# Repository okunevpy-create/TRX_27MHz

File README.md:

# TRX 27 MHz — самодельная КВ/СВ радиостанция

Модульная радиостанция диапазона 27 МГц (AM + SSB фазовым методом) для автомобиля и автономной работы.

## Назначение
- Связь на частотах дальнобойщиков (15-й канал, 27.135 МГц, AM).
- Радиолюбительские связи SSB (вызывная 27.190 МГц).

## Ограничения и риски
- **Мощность**: AM — не более 4 Вт (несущая), SSB — не более 12 Вт (пиковая). Ограничитель AM — обязателен, отключаемый через физический тумблер LIMIT/FULL на УМ.
- **Термостабильность SSB**: открытый вопрос, решается отдельной сессией (кварц Si5351 ±20 ppm).
- **Регуляторика**: безлицензионная СиБи в РФ; отключение ограничителя AM — осознанное действие пользователя.

## Этапы и подэтапы
| Этап | Название | Папка | Подэтапы |
|------|----------|-------|----------|
| **0** | Мастер-лист (интерфейсы) | `KiCad/00_master` | — |
| **1** | Плата управления | `KiCad/01_control` | 1.1–1.5 |
| **2** | Усилитель мощности | `KiCad/02_power_amp` | 2.1–2.4 |
| **3** | Тракт RX/TX | `KiCad/03_rx_tx` | 3.1–3.5 |
| **4** | Корпусирование | `Mechanical/` | 4.1–4.5 |

## Рекомендуемый порядок работ
1. **Этап 0** — мастер-лист: иерархия и все межблочные сигналы.
2. Зафиксировать контракты (`docs/contracts/`).
3. Схемотехника 1.1–1.4.
4. Схемотехника 2.1–2.2.
5. **Совместно** 1.5 + 2.3 (PTT, I_sense, SWR_sense, PWR_LIMIT_EN/SW, RX_audio).
6. ⚠️ **Только теперь** — травление и монтаж платы этапа 1.
7. Доделать 2.4 (тепловой расчёт).
8. Этап 3 (3.1–3.5).
9. Этап 4 (4.1–4.5).

> **⚠️ Важно:** изготовление платы этапа 1 (травление, монтаж) начинается **только после** завершения совместных работ 1.5 + 2.3 и фиксации контракта `control_pa.md`. До этого — только схемотехника и разводка в KiCad, без травления.

## Структура
- `docs/` — документация, контракты, BOM, расчёты.
- `Firmware/` — прошивка (PlatformIO, STM32F411).
- `KiCad/` — проекты плат, локальные библиотеки.
- `Mechanical/` — корпус, панели, крепления (FreeCAD).

## Быстрые ссылки
- [Архитектура и декомпозиция](docs/block-diagram.md)
- [Питание](docs/power-distribution.md)
- [Контракты](docs/contracts/README.md)
- [BOM](docs/bom/README.md)
- [Расчёты](docs/calculations/README.md)
- [Контекст для сессий](docs/context.md)
- [Оборудование](docs/equipment.md)
- [Распиновка](docs/inter-module-pinout.md)
- [Каналы](docs/channels.md)
- [KiCad](KiCad/README.md)
- [Прошивка](Firmware/README.md)
- [Механика](Mechanical/README.md)

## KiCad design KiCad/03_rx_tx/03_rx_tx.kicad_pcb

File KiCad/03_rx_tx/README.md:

# 03_rx_tx — тракт RX/TX (этап 3)

## Подэтапы
- **3.1** — BPF 27 МГц
- **3.2** — Смеситель + ПЧ 10 МГц + кварцевый фильтр
- **3.3** — Детектор AM/SSB + УНЧ + защита входа RX (диоды + аттенюатор); разъём `J9` (XH2.54 2P) под проводной монтаж: SP+ и GND (к корпусному разъёму 3.5 мм); вход `MUTE` (управление mute-транзистором на входе LM386)
- **3.4** — Формирователь SSB (фильтровый метод: DSB @10 МГц → кварцевый фильтр) + драйвер TX 2SC2314; модулятор принимает `MIC_LINE` с `01_control`
- **3.5** — Питание: 12 В → LM7809 → локальные LDO

## Назначение
- Смеситель на SA612.
- ПЧ 10 МГц + кварцевый фильтр.
- Детектор AM/SSB, УНЧ на LM386.
- Формирователь SSB фильтровым методом (балансный модулятор NE612 DSB @10 МГц → лестничный кварцевый фильтр).
- BPF 27 МГц.
- Защита входа RX от просачивания при передаче.

## Контракт
- `docs/contracts/control_rxtx.md` — VFO, BFO, MODE, RX_audio, PTT, 12 В.

## FM
Не делаем (решено 2026-10-31).

## Статус
Заготовка. Заполняется после этапа 2.

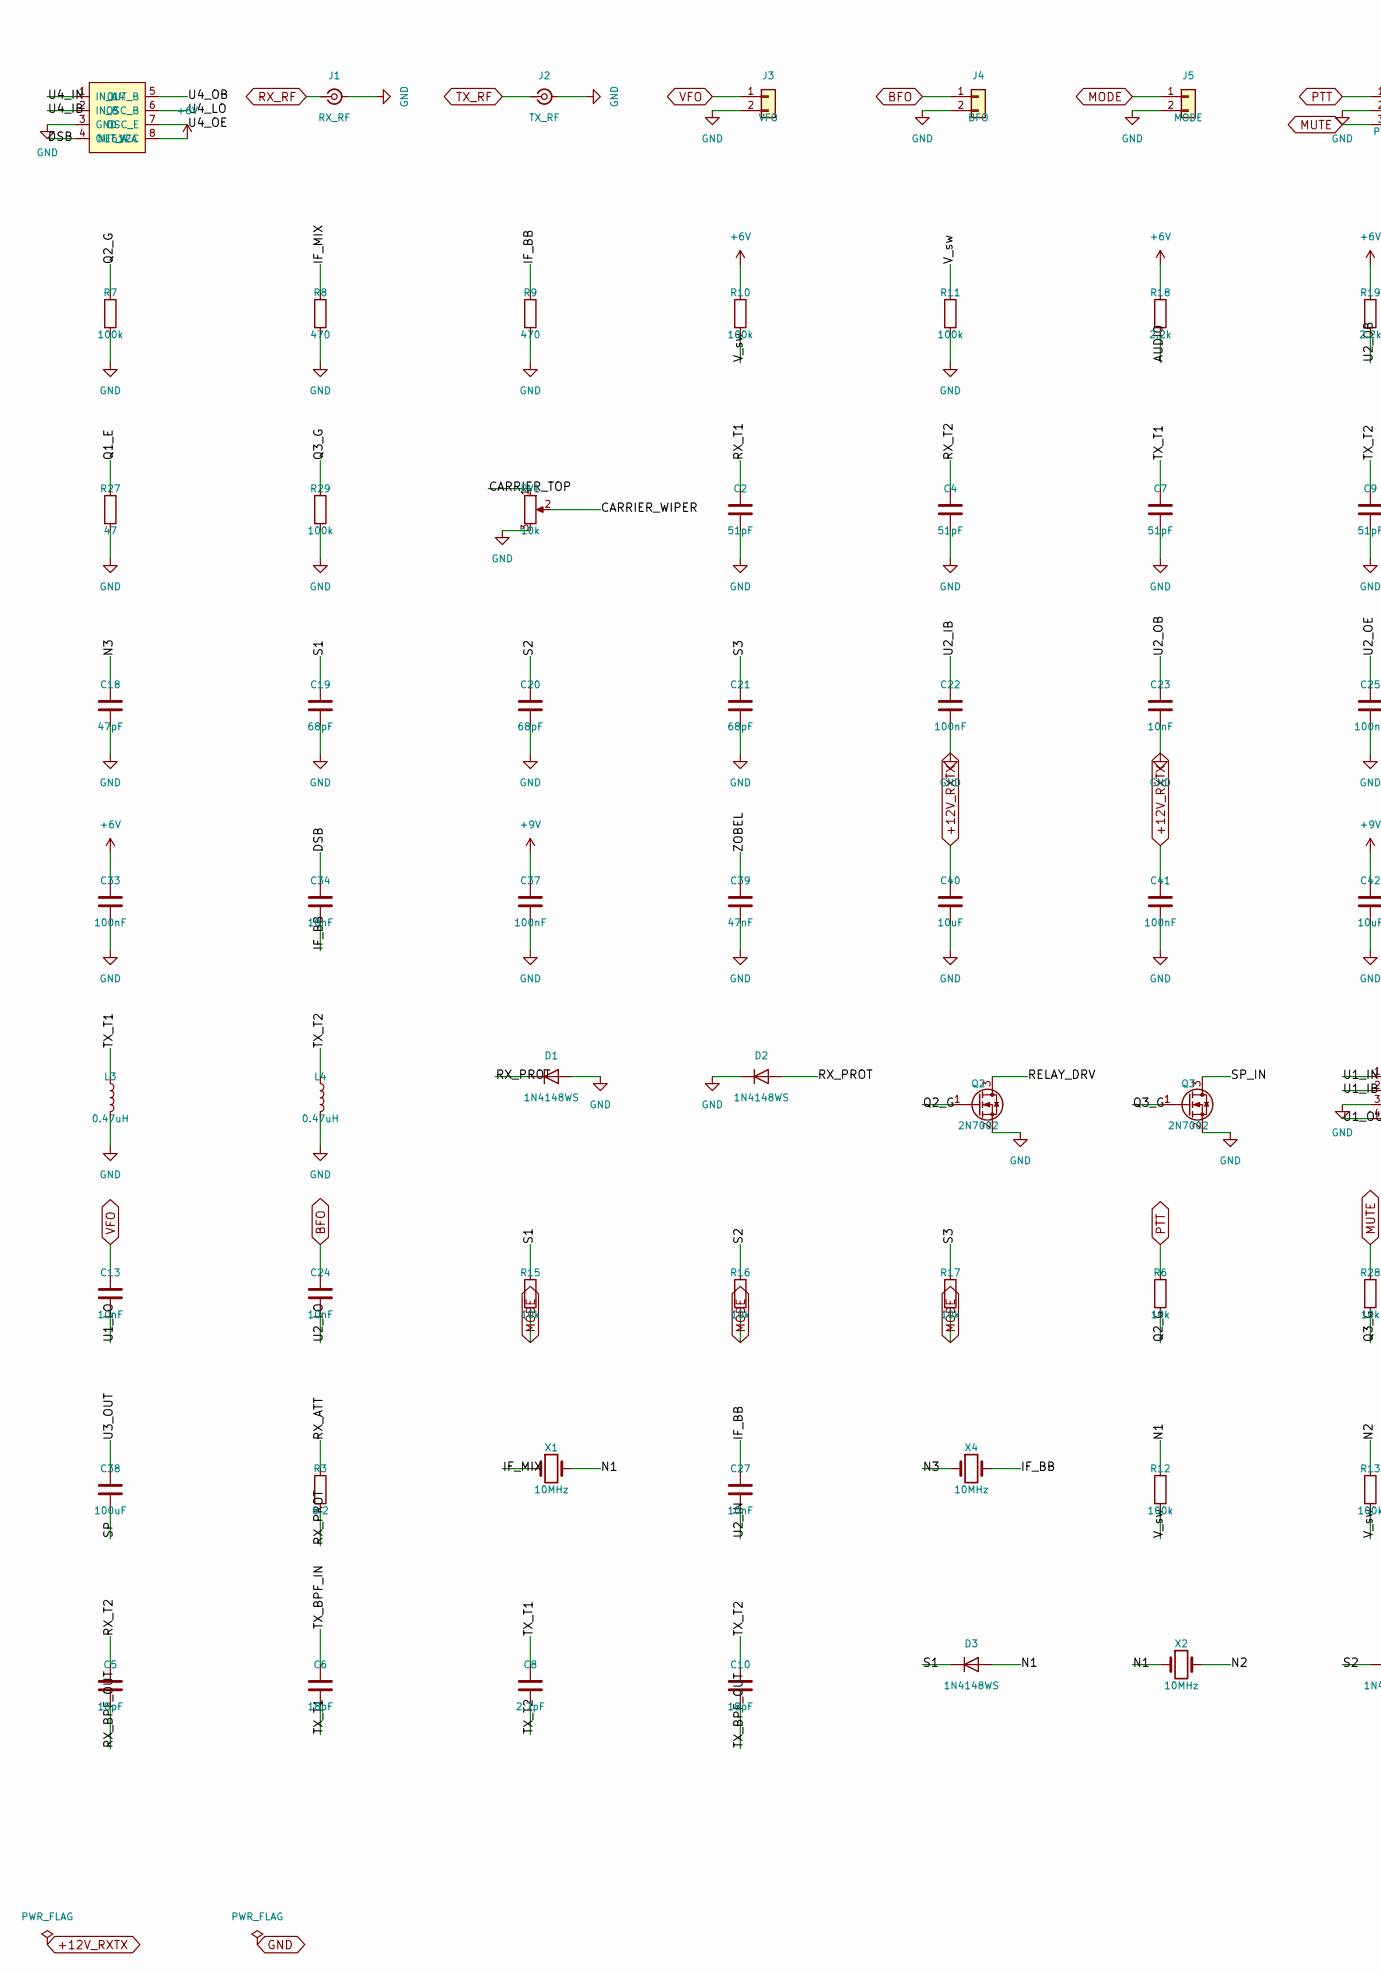
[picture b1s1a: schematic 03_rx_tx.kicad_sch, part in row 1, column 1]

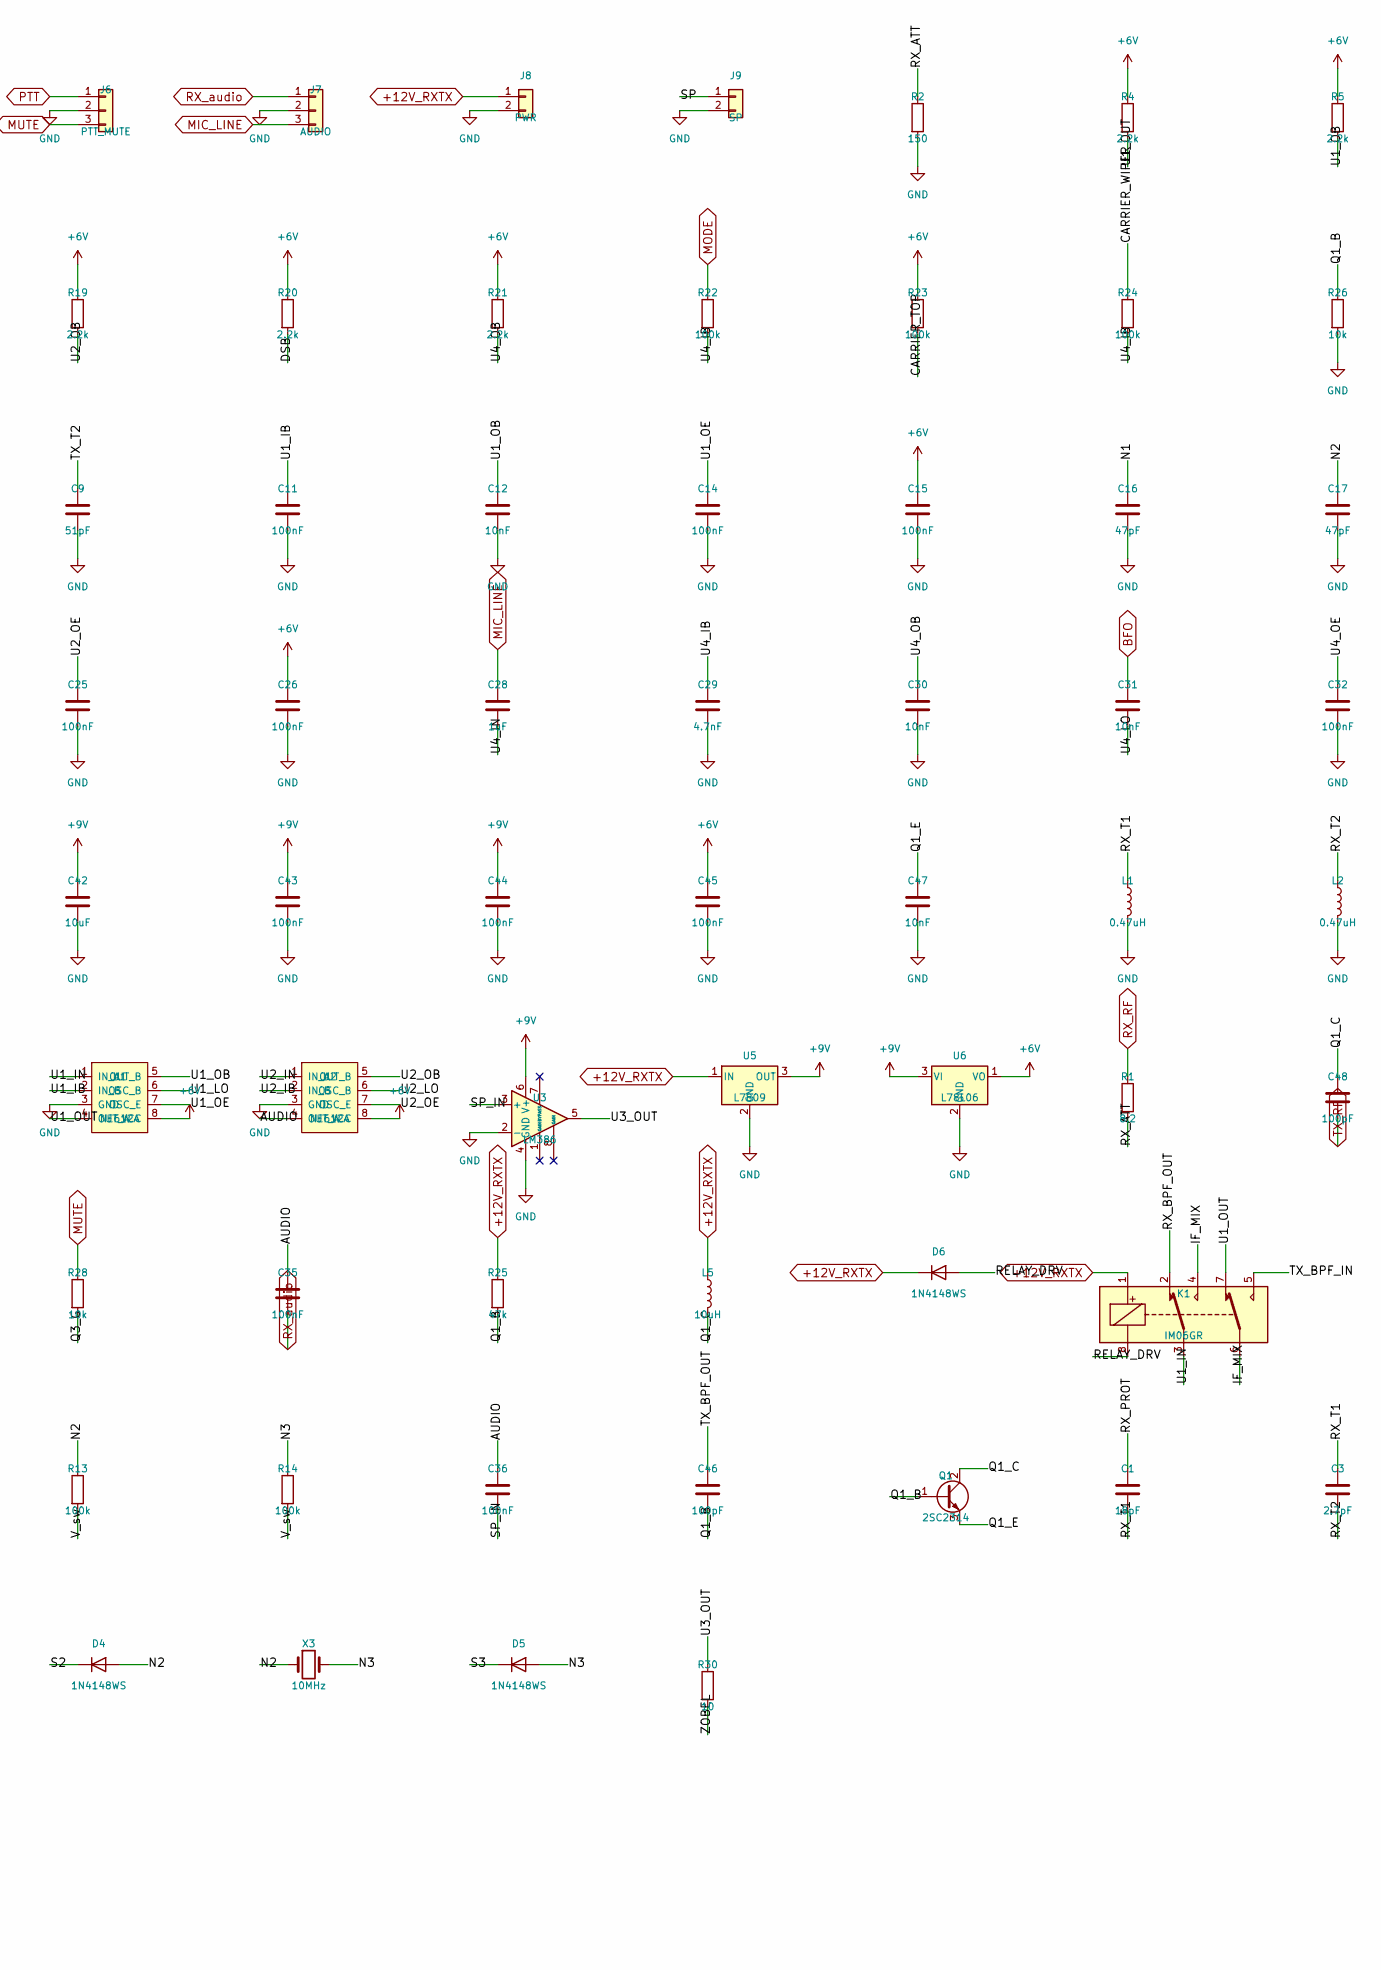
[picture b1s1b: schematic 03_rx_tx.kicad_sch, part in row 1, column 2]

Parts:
C1, C5, C6, C10: 18pF; C_0805_2012Metric_Pad1.18x1.45mm_HandSolder
C2, C4, C7, C9: 51pF; C_0805_2012Metric_Pad1.18x1.45mm_HandSolder
C3, C8: 2.7pF; C_0805_2012Metric_Pad1.18x1.45mm_HandSolder
C11, C14, C15, C22, C25, C26, C32, C33, C35, C36, C37, C41, C43, C44, C45: 100nF; C_0603_1608Metric_Pad1.08x0.95mm_HandSolder
C12, C13, C23, C24, C27, C30, C31, C34, C47: 10nF; C_0603_1608Metric_Pad1.08x0.95mm_HandSolder
C16, C17, C18: 47pF; C_0603_1608Metric_Pad1.08x0.95mm_HandSolder
C19, C20, C21: 68pF; C_0603_1608Metric_Pad1.08x0.95mm_HandSolder
C28: 1uF; C_0603_1608Metric_Pad1.08x0.95mm_HandSolder
C29: 4.7nF; C_0603_1608Metric_Pad1.08x0.95mm_HandSolder
C38: 100uF; CP_Elec_6.3x5.3
C39: 47nF; C_0603_1608Metric_Pad1.08x0.95mm_HandSolder
C40, C42: 10uF; CP_Elec_6.3x5.3
C46, C48: 100pF; C_0603_1608Metric_Pad1.08x0.95mm_HandSolder
D1, D2, D3, D4, D5, D6: 1N4148WS; D_SOD-323F
J1: RX_RF; SMA_S-P215
J2: TX_RF; SMA_S-P215
J3: VFO; SMA_S-P215
J4: BFO; SMA_S-P215
J5: MODE; JST_XH_B2B-XH-A_1x02_P2.50mm_Vertical
J6: PTT_MUTE; JST_XH_B3B-XH-A_1x03_P2.50mm_Vertical
J7: AUDIO; JST_XH_B3B-XH-A_1x03_P2.50mm_Vertical
J8: PWR; TerminalBlock_Phoenix_MKDS-1,5-2_1x02_P5.00mm_Horizontal
J9: SP; JST_XH_B2B-XH-A_1x02_P2.50mm_Vertical
K1: IM06GR; Relay_DPDT_AXICOM_IM06GR_GullWing
L1, L2, L3, L4: 0.47uH; L_0805_2012Metric_Pad1.05x1.20mm_HandSolder
L5: 10uH; L_0805_2012Metric_Pad1.05x1.20mm_HandSolder
Q1: 2SC2314; TO-92L_HandSolder
Q2, Q3: 2N7002; SOT-23_Handsoldering
R1, R3: 8.2; R_0603_1608Metric_Pad0.98x0.95mm_HandSolder
R2: 150; R_0603_1608Metric_Pad0.98x0.95mm_HandSolder
R4, R5, R18, R19, R20, R21: 2.2k; R_0603_1608Metric_Pad0.98x0.95mm_HandSolder
R6, R15, R16, R17, R26, R28: 10k; R_0603_1608Metric_Pad0.98x0.95mm_HandSolder
R7, R10, R11, R12, R13, R14, R22, R23, R24, R29: 100k; R_0603_1608Metric_Pad0.98x0.95mm_HandSolder
R8, R9: 470; R_0603_1608Metric_Pad0.98x0.95mm_HandSolder
R25: 47k; R_0603_1608Metric_Pad0.98x0.95mm_HandSolder
R27: 47; R_0603_1608Metric_Pad0.98x0.95mm_HandSolder
R30: 10; R_0603_1608Metric_Pad0.98x0.95mm_HandSolder
RV1: 10k; Potentiometer_Bourns_3214W_Vertical
U1, U2, U4: NE612A; SOIC-8_3.9x4.9mm_P1.27mm
U3: LM386; SOIC-8_3.9x4.9mm_P1.27mm
U5: L7809; TO-220-3_Vertical
U6: L78L06; TO-92_Inline
X1, X2, X3, X4: 10MHz; Crystal_SMD_HC49-SD_HandSoldering

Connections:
+6V: C15.1, C26.1, C33.1, C45.1, R4.1, R5.1, R10.1, R18.1, R19.1, R20.1, R21.1, R23.1, U1.8 (VCC), U2.8 (VCC), U4.8 (VCC), U6.1 (VO)
+9V: C37.1, C42.1, C43.1, C44.1, U3.6 (V+), U5.3 (OUT), U6.3 (VI)
+12V_RXTX: C40.1, C41.1, D6.1 (K), J8.1, K1.1, L5.1, R25.1, U5.1 (IN)
/AUDIO: C35.1, C36.1, R18.2, U2.4 (OUT_A)
/CARRIER_TOP: R23.2, RV1.1
/CARRIER_WIPER: R24.1, RV1.2
/DSB: C34.1, R20.2, U4.4 (OUT_A)
/IF_BB: C27.1, C34.2, R9.1, X4.2
/IF_MIX: K1.4, K1.6, R8.1, X1.1
/N1: C16.1, D3.2 (A), R12.1, X1.2, X2.1
/N2: C17.1, D4.2 (A), R13.1, X2.2, X3.1
/N3: C18.1, D5.2 (A), R14.1, X3.2, X4.1
/Q1_B: C46.2, Q1.1 (B), R25.2, R26.1
/Q1_C: C48.1, L5.2, Q1.2 (C)
/Q1_E: C47.1, Q1.3 (E), R27.1
/Q2_G: Q2.1 (G), R6.2, R7.1
/Q3_G: Q3.1 (G), R28.2, R29.1
/RELAY_DRV: D6.2 (A), K1.8, Q2.3 (D)
/RX_ATT: R1.2, R2.1, R3.1
/RX_BPF_OUT: C5.2, K1.2
/RX_PROT: C1.1, D1.1 (K), D2.2 (A), R3.2
/RX_T1: C1.2, C2.1, C3.1, L1.1
/RX_T2: C3.2, C4.1, C5.1, L2.1
/S1: C19.1, D3.1 (K), R15.1
/S2: C20.1, D4.1 (K), R16.1
/S3: C21.1, D5.1 (K), R17.1
/SP: C38.2, J9.1
/SP_IN: C36.2, Q3.3 (D), U3.3 (+)
/TX_BPF_IN: C6.1, K1.5
/TX_BPF_OUT: C10.2, C46.1
/TX_T1: C6.2, C7.1, C8.1, L3.1
/TX_T2: C8.2, C9.1, C10.1, L4.1
/U1_IB: C11.1, U1.2 (IN_B)
/U1_IN: K1.3, U1.1 (IN_A)
/U1_LO: C13.2, U1.6 (OSC_B)
/U1_OB: C12.1, R5.2, U1.5 (OUT_B)
/U1_OE: C14.1, U1.7 (OSC_E)
/U1_OUT: K1.7, R4.2, U1.4 (OUT_A)
/U2_IB: C22.1, U2.2 (IN_B)
/U2_IN: C27.2, U2.1 (IN_A)
/U2_LO: C24.2, U2.6 (OSC_B)
/U2_OB: C23.1, R19.2, U2.5 (OUT_B)
/U2_OE: C25.1, U2.7 (OSC_E)
/U3_OUT: C38.1, R30.1, U3.5
/U4_IB: C29.1, R22.2, R24.2, U4.2 (IN_B)
/U4_IN: C28.2, U4.1 (IN_A)
/U4_LO: C31.2, U4.6 (OSC_B)
/U4_OB: C30.1, R21.2, U4.5 (OUT_B)
/U4_OE: C32.1, U4.7 (OSC_E)
/V_sw: R10.2, R11.1, R12.2, R13.2, R14.2
/ZOBEL: C39.1, R30.2
BFO: C24.1, C31.1, J4.1
GND: C2.2, C4.2, C7.2, C9.2, C11.2, C12.2, C14.2, C15.2, C16.2, C17.2, C18.2, C19.2, C20.2, C21.2, C22.2, C23.2, C25.2, C26.2, C29.2, C30.2, C32.2, C33.2, C37.2, C39.2, C40.2, C41.2, C42.2, C43.2, C44.2, C45.2, C47.2, D1.2 (A), D2.1 (K), J1.2 (Ext), J2.2 (Ext), J3.2, J4.2, J5.2, J6.2, J7.2, J8.2, J9.2, L1.2, L2.2, L3.2, L4.2, Q2.2 (S), Q3.2 (S), R2.2, R7.2, R8.2, R9.2, R11.2, R26.2, R27.2, R29.2, RV1.3, U1.3 (GND), U2.3 (GND), U3.2 (-), U3.4 (GND), U4.3 (GND), U5.2 (GND), U6.2 (GND)
MIC_LINE: C28.1, J7.3
MODE: J5.1, R15.2, R16.2, R17.2, R22.1
MUTE: J6.3, R28.1
PTT: J6.1, R6.1
RX_RF: J1.1 (In), R1.1
RX_audio: C35.2, J7.1
TX_RF: C48.2, J2.1 (In)
VFO: C13.1, J3.1

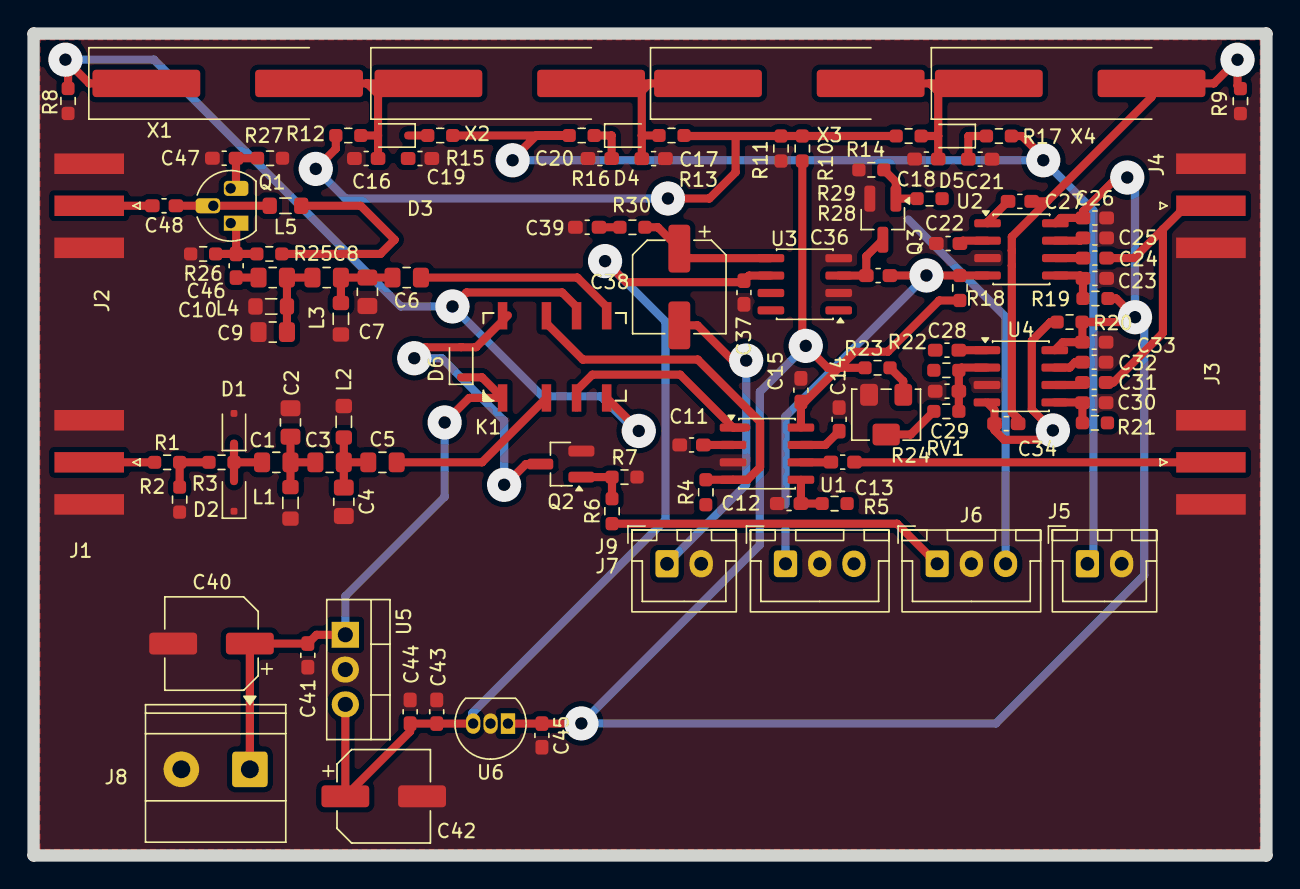
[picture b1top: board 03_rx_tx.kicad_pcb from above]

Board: 2 copper layers, 90.0 x 60.0 mm, 113 parts (1 on the bottom side), 61 nets.

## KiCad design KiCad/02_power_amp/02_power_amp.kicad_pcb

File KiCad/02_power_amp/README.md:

# 02_power_amp — усилитель мощности (этап 2)

## Подэтапы
- **2.1** — Драйвер + 2× RD16HHF1 (push-pull, класс AB)
- **2.2** — ФНЧ 27 МГц (5-го порядка)
- **2.3** — Датчики тока/КСВ + тумблер LIMIT/FULL + подстроечник + светодиод + вход PWR_LIMIT_EN + выход PWR_LIMIT_SW
- **2.4** — Тепловой расчёт + радиатор

## Назначение
- ~10–15 Вт на 50 Ом при раскачке ~0,5 Вт.
- В AM — ограничение до 4 Вт (тумблер LIMIT + подстроечник).
- Питание: 12 В напрямую через LC-фильтр.
- Радиатор обязателен.

## T/R switch и антенна
- **Реле на `02_power_amp`**, антенный разъём J_ANT_1 — здесь.
- Управление — PTT с `01_control`.

## Контракт
- `docs/contracts/control_pa.md` — PTT, I_sense, SWR_sense, PWR_LIMIT_EN, PWR_LIMIT_SW, 12 В.

## Связь с этапом 1
Подэтап **2.3** разводится совместно с **1.5**, до изготовления платы этапа 1.

## Статус
Заготовка. Схемотехника 2.1–2.2 — после 1.4.

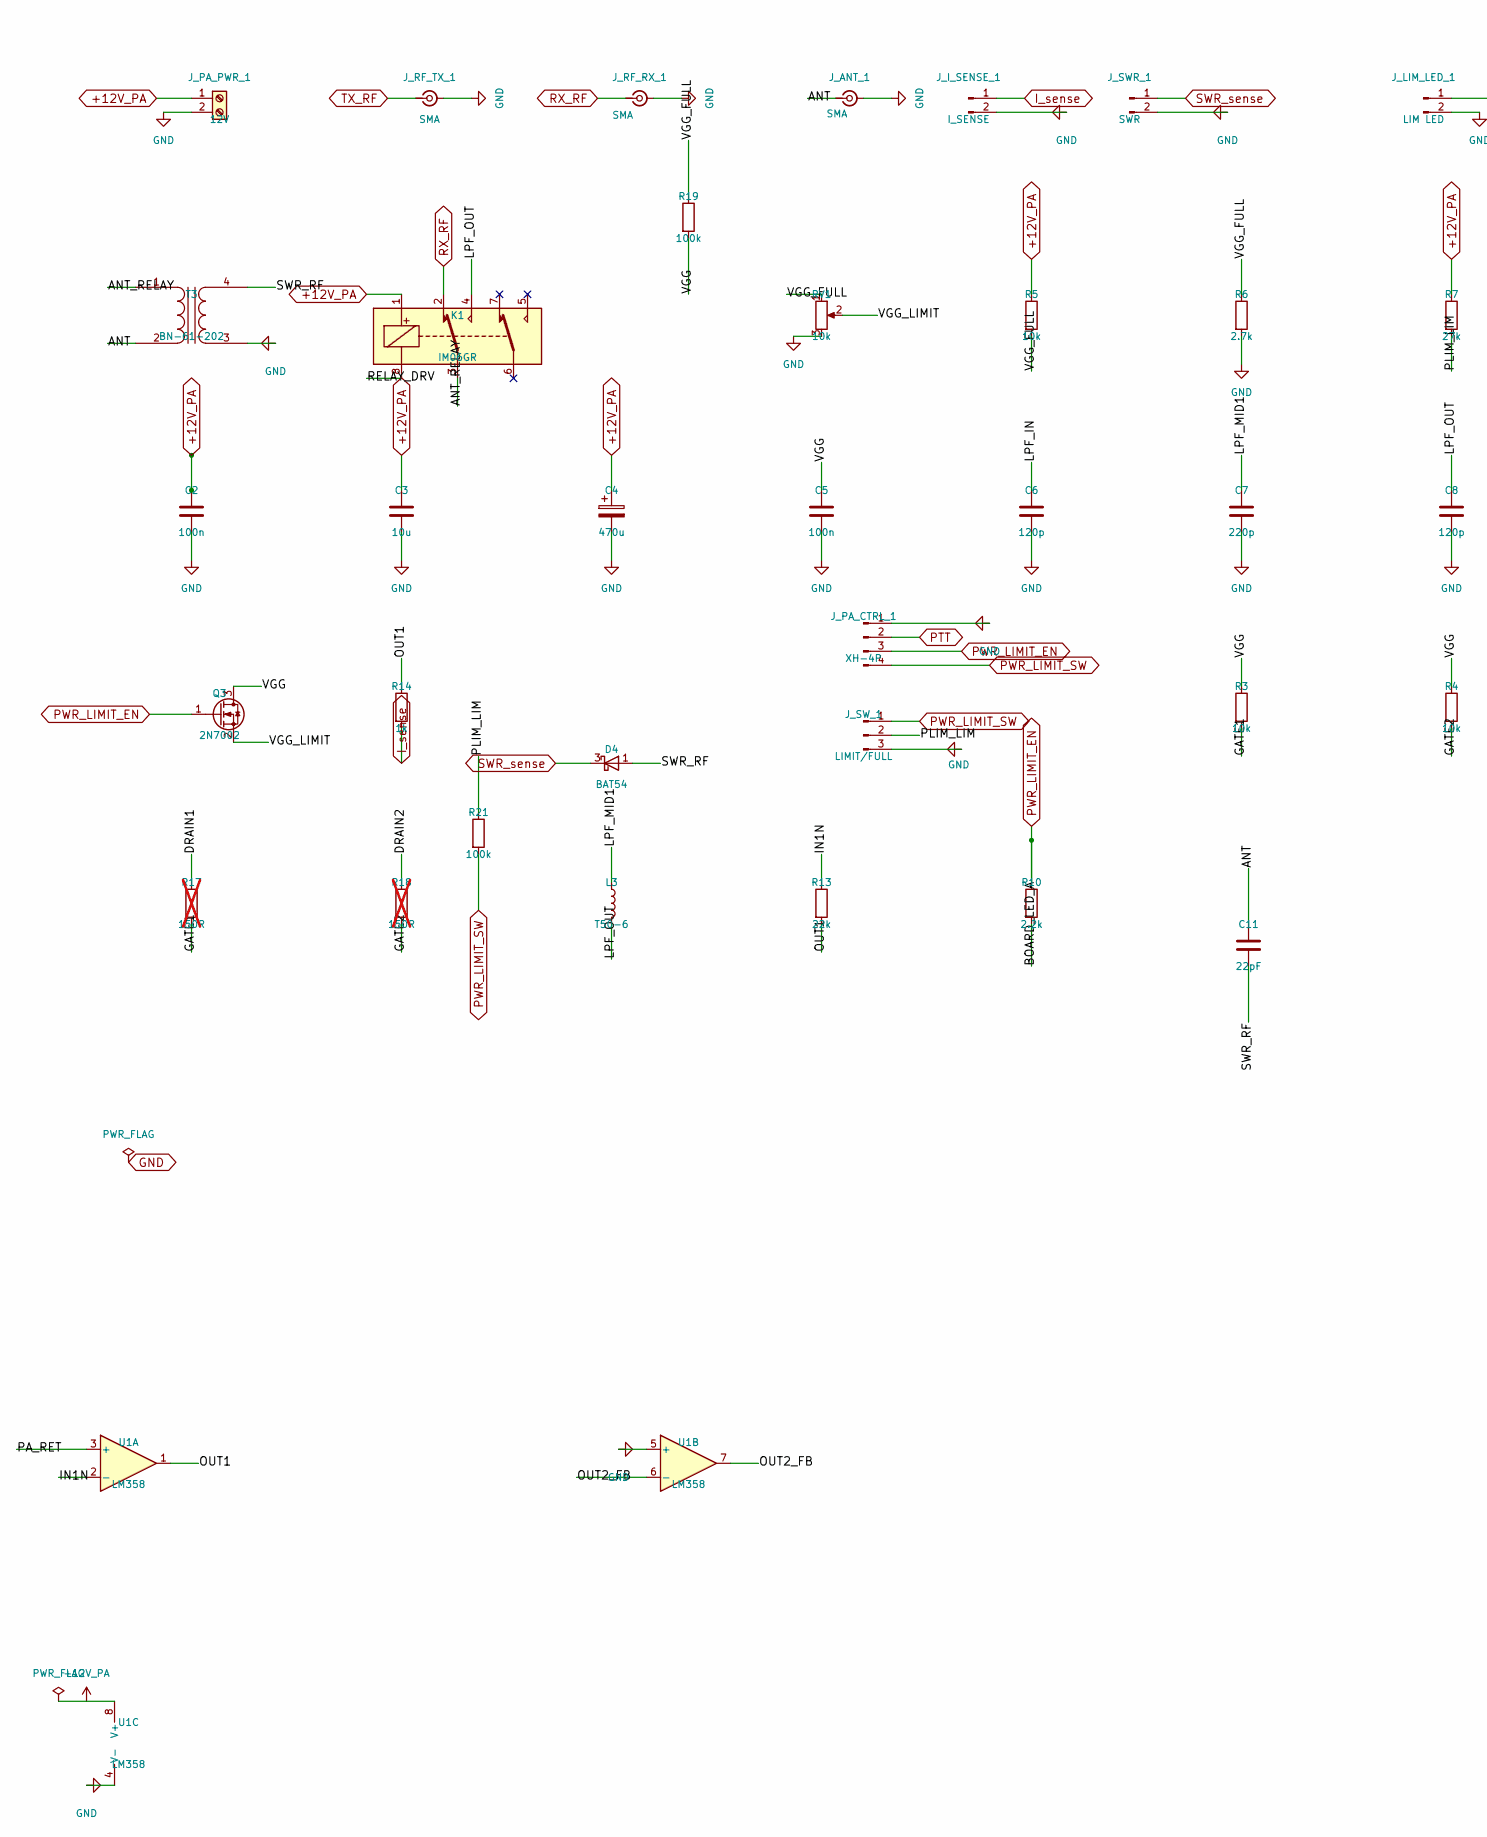
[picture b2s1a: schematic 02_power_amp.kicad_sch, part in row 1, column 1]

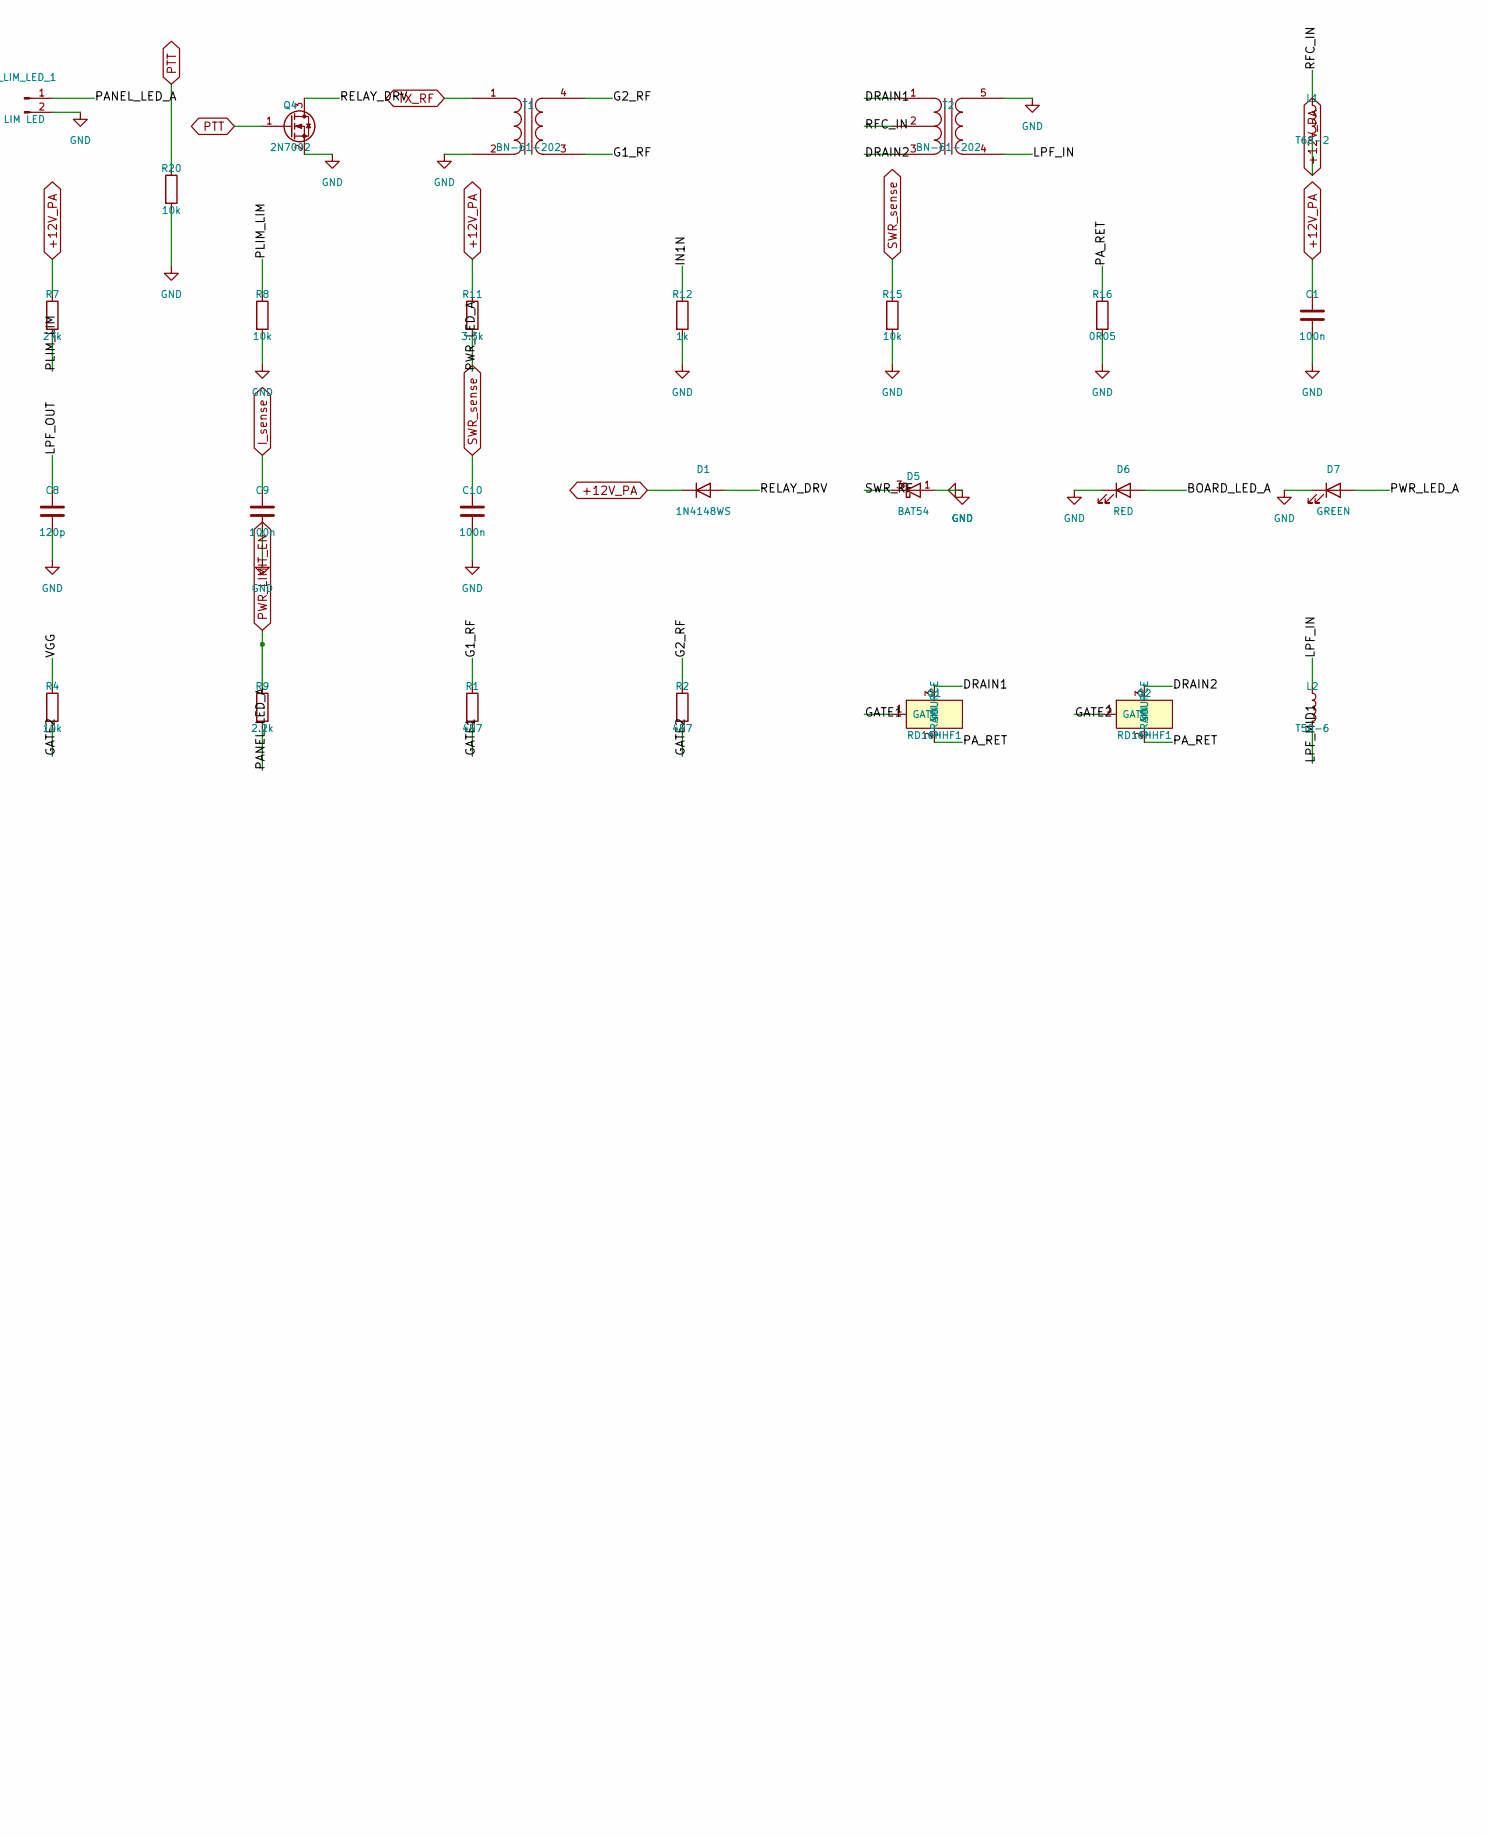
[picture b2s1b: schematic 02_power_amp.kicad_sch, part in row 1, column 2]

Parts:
C1, C2, C5, C9, C10: 100n; C_0603_1608Metric_Pad1.08x0.95mm_HandSolder
C3: 10u; C_0805_2012Metric_Pad1.18x1.45mm_HandSolder
C4: 470u; CP_Elec_10x10.5
C6, C8: 120p; C_0805_2012Metric_Pad1.18x1.45mm_HandSolder
C7: 220p; C_0805_2012Metric_Pad1.18x1.45mm_HandSolder
C11: 22pF; C_0805_2012Metric_Pad1.18x1.45mm_HandSolder
D1: 1N4148WS; D_SOD-323F
D4, D5: BAT54; SOT-23-3
D6: RED; LED_0805_2012Metric_Pad1.15x1.40mm_HandSolder
D7: GREEN; LED_0805_2012Metric_Pad1.15x1.40mm_HandSolder
J_ANT_1: SMA; SMA_S-P215
J_I_SENSE_1: I_SENSE; JST_XH_B2B-XH-A_1x02_P2.50mm_Vertical
J_LIM_LED_1: LIM LED; JST_XH_B2B-XH-A_1x02_P2.50mm_Vertical
J_PA_CTRL_1: XH-4P; JST_XH_B4B-XH-A_1x04_P2.50mm_Vertical
J_PA_PWR_1: 12V; TerminalBlock_Phoenix_MKDS-1,5-2_1x02_P5.00mm_Horizontal
J_RF_RX_1: SMA; SMA_S-P215
J_RF_TX_1: SMA; SMA_S-P215
J_SWR_1: SWR; JST_XH_B2B-XH-A_1x02_P2.50mm_Vertical
J_SW_1: LIMIT/FULL; JST_XH_B3B-XH-A_1x03_P2.50mm_Vertical
K1: IM06GR; Relay_DPDT_AXICOM_IM06GR_GullWing
L1: T68-2; L_Toroid_Vertical_L17.8mm_W8.1mm_P7.62mm_Bourns_5700
L2, L3: T50-6; L_Toroid_Vertical_L13.0mm_W6.5mm_P5.60mm
Q1, Q2: RD16HHF1; TO-220-3_Vertical
Q3, Q4: 2N7002; SOT-23_Handsoldering
R1, R2: 4R7; R_0603_1608Metric_Pad0.98x0.95mm_HandSolder
R3, R4, R5, R8, R15, R20: 10k; R_0603_1608Metric_Pad0.98x0.95mm_HandSolder
R6: 2.7k; R_0603_1608Metric_Pad0.98x0.95mm_HandSolder
R7: 27k; R_0603_1608Metric_Pad0.98x0.95mm_HandSolder
R9, R10: 2.2k; R_0603_1608Metric_Pad0.98x0.95mm_HandSolder
R11: 3.3k; R_0603_1608Metric_Pad0.98x0.95mm_HandSolder
R12, R14: 1k; R_0603_1608Metric_Pad0.98x0.95mm_HandSolder
R13: 22k; R_0603_1608Metric_Pad0.98x0.95mm_HandSolder
R16: 0R05; R_2512_6332Metric
R17, R18: 150R; R_0603_1608Metric_Pad0.98x0.95mm_HandSolder; not fitted
R19, R21: 100k; R_0603_1608Metric_Pad0.98x0.95mm_HandSolder
RV1: 10k; Potentiometer_Bourns_3296W_Vertical
T1, T3: BN-61-202; PinHeader_1x04_P2.54mm_Vertical
T2: BN-61-202; PinHeader_1x05_P2.54mm_Vertical
U1: LM358; SOIC-8_3.9x4.9mm_P1.27mm

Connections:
+12V_PA: C1.1, C2.1, C3.1, C4.1, D1.1 (K), J_PA_PWR_1.1, K1.1, L1.2, R5.1, R7.1, R11.1, U1.8 (V+)
/ANT: C11.1, J_ANT_1.1 (In), T3.2 (AB)
/ANT_RELAY: K1.3, T3.1 (AA)
/BOARD_LED_A: D6.2 (A), R10.2
/DRAIN1: Q1.3 (DRAIN), R17.1, T2.1 (PR1)
/DRAIN2: Q2.3 (DRAIN), R18.1, T2.3 (PR2)
/G1_RF: R1.1, T1.3 (SA)
/G2_RF: R2.1, T1.4 (SB)
/GATE1: Q1.1 (GATE), R1.2, R3.2, R17.2
/GATE2: Q2.1 (GATE), R2.2, R4.2, R18.2
/IN1N: R12.1, R13.1, U1.2 (-)
/LPF_IN: C6.1, L2.1, T2.4 (S1)
/LPF_MID1: C7.1, L2.2, L3.1
/LPF_OUT: C8.1, K1.4, L3.2
/OUT1: R13.2, R14.1, U1.1
/OUT2_FB: U1.6 (-), U1.7
/PANEL_LED_A: J_LIM_LED_1.1, R9.2
/PA_RET: Q1.2 (SOURCE), Q2.2 (SOURCE), R16.1, U1.3 (+)
/PLIM_LIM: J_SW_1.2, R7.2, R8.1, R21.1
/PWR_LED_A: D7.2 (A), R11.2
/RELAY_DRV: D1.2 (A), K1.8, Q4.3 (D)
/RFC_IN: L1.1, T2.2 (PM)
/SWR_RF: C11.2, D4.1 (A), D5.3 (K), T3.4 (SB)
/VGG: C5.1, Q3.3 (D), R3.1, R4.1, R19.2
/VGG_FULL: R5.2, R6.1, R19.1, RV1.1
/VGG_LIMIT: Q3.2 (S), RV1.2
GND: C1.2, C2.2, C3.2, C4.2, C5.2, C6.2, C7.2, C8.2, C9.2, C10.2, D5.1 (A), D6.1 (K), D7.1 (K), J_ANT_1.2 (Ext), J_I_SENSE_1.2, J_LIM_LED_1.2, J_PA_CTRL_1.1, J_PA_PWR_1.2, J_RF_RX_1.2 (Ext), J_RF_TX_1.2 (Ext), J_SWR_1.2, J_SW_1.3, Q4.2 (S), R6.2, R8.2, R12.2, R15.2, R16.2, R20.2, RV1.3, T1.2 (AB), T2.5 (S2), T3.3 (SA), U1.4 (V-), U1.5 (+)
I_sense: C9.1, J_I_SENSE_1.1, R14.2
PTT: J_PA_CTRL_1.2, Q4.1 (G), R20.1
PWR_LIMIT_EN: J_PA_CTRL_1.3, Q3.1 (G), R9.1, R10.1
PWR_LIMIT_SW: J_PA_CTRL_1.4, J_SW_1.1, R21.2
RX_RF: J_RF_RX_1.1 (In), K1.2
SWR_sense: C10.1, D4.3 (K), J_SWR_1.1, R15.1
TX_RF: J_RF_TX_1.1 (In), T1.1 (AA)

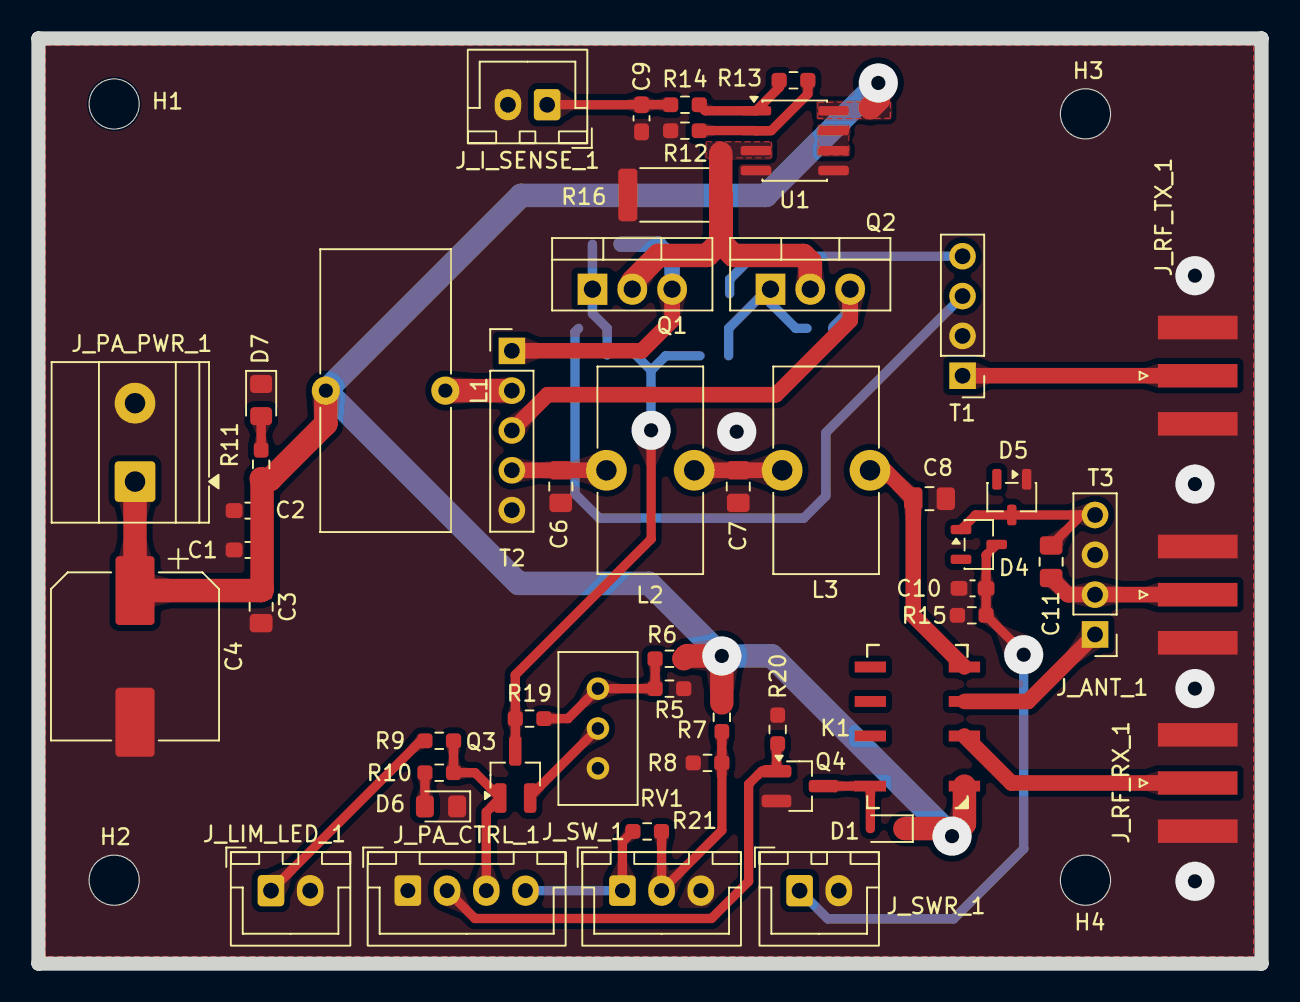
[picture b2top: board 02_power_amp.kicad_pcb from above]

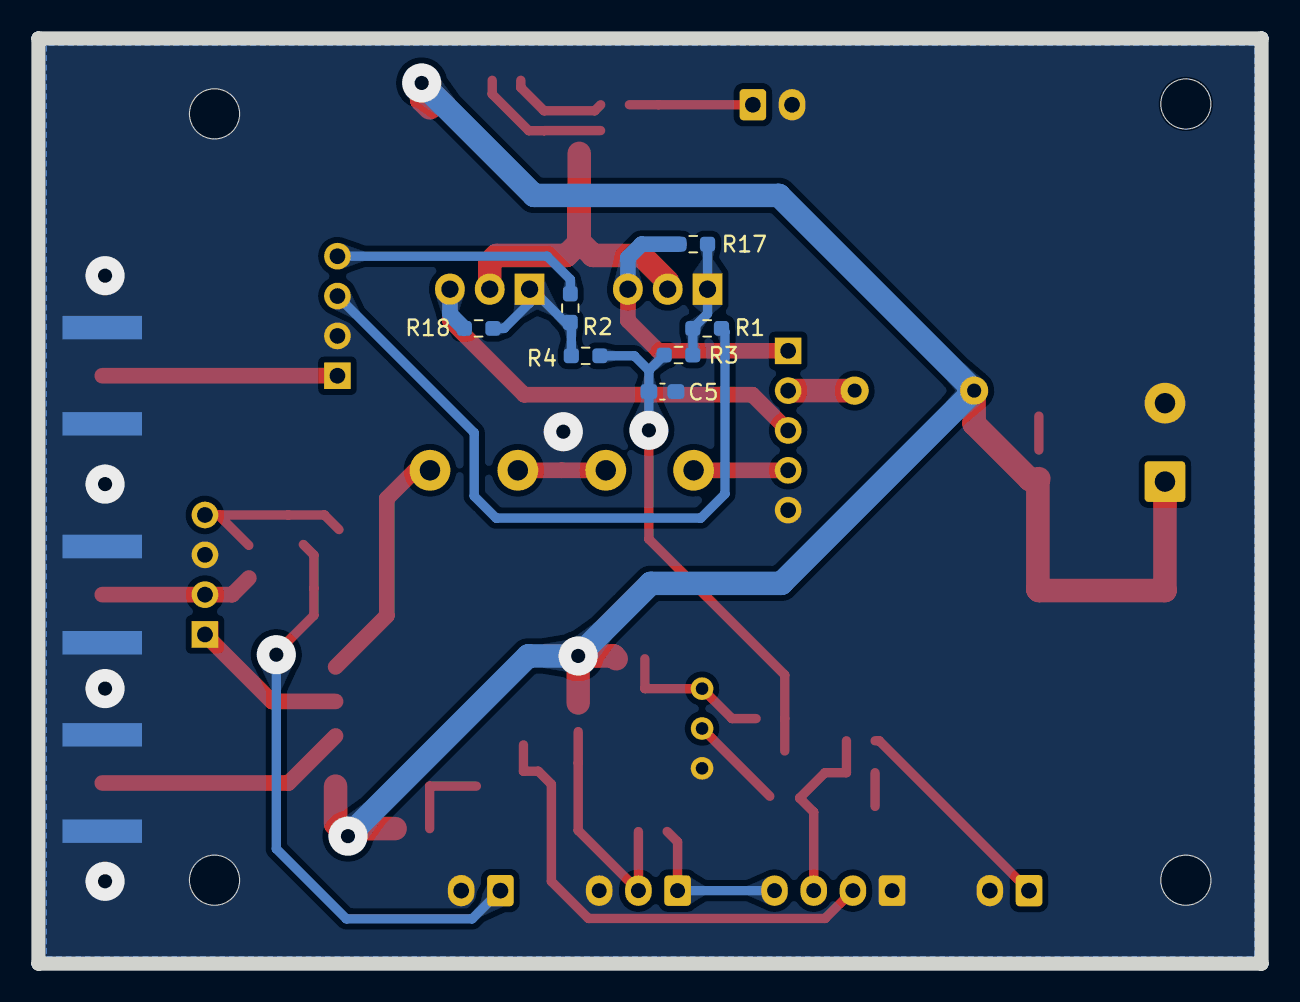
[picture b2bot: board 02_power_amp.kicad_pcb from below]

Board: 2 copper layers, 78.0 x 59.0 mm, 63 parts (7 on the bottom side), 34 nets.

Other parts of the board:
H1, H2, H3, H4: MountingHole_3.2mm_M3
